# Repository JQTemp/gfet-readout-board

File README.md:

# Nanoamp readout for graphene FET sensors

A low-noise data acquisition board that measures currents of a few nanoamps from a graphene field-effect transistor chip. I led the electronics and took the board through two hardware versions.

| | |
|---|---|
| My role | Electronics lead, covering circuit design, layout, enclosure, bench testing and test software |
| Channels | 6 on V2, 14 on V1 |
| Current range | 5 to 25 nA |
| Resolution | 0.5 nA, measured |
| Inaccuracy | 0.05 to 0.1% in initial bench tests |
| Conversion | MCP3208, 12-bit, SPI, 3.3 V reference |
| Board | Two layers, 79 × 74 mm |
| Tools | KiCad, 3D printing, Python with PyVISA, MATLAB, Keithley source-measure units and multimeter |

## Context

I led the electronics for DeTectUs, a multidisciplinary DTU team taking part in SensUs, an international student competition for sensor prototypes. The team built its sensor around a commercial graphene FET chip from Graphenea with 14 channels. Most of the team worked on functionalising the graphene surface, while I was responsible for the hardware that reads the chip out.

The board holds each channel at a small fixed bias, sweeps the gate voltage and records the channel current, which sits between 5 and 25 nA. The signal is a shift in the gate voltage where the current reaches its minimum, known as the Dirac point.

## Signal chain

Every channel runs through the same chain. A TLC2274 transimpedance amplifier turns the channel current into a voltage, a second TLC2274 stage inverts it into the range of the ADC and an RC low-pass filter at about 10 Hz removes interference and prevents aliasing. A 12-bit MCP3208 ADC converts all six channels and a Raspberry Pi 4 reads it over SPI.

An external 12 V supply keeps mains conversion off the board. An MCP1702 LDO makes 5 V, a MAX1673 charge pump makes −5 V for the op-amps and an LP2950 LDO makes 3.3 V for the ADC and the digital potentiometer. A MAX6250 precision reference and a resistor divider set a fixed 100 mV channel bias. The on-board gate potentiometer was not finished in time, so a bench source-measure unit swept the gate during testing.

## From V1 to V2

V1 was a 154 × 121 mm board with 14 channels, an STM32 Nucleo board for conversion and control and two SPI digital potentiometers for the gate and bias. Measurements on the chips showed that channels 8 to 14 gave unstable readings. V2 reads six channels, adds the inverting stage, moves conversion to a dedicated 12-bit ADC and hands control to a Raspberry Pi 4. The chip socket sits next to the analog front end, the power section runs along the bottom edge and the bottom layer is a ground pour.

## Enclosure

I also designed the enclosure that turns the board into a standalone device. The 3D-printed base, 200 × 154 mm, holds the readout board next to a Raspberry Pi 4, and a tilted housing above them carries the display. The front stays open, so the chip socket can be reached to swap chips.

| Base with the V2 board and a Raspberry Pi 4 | With the display housing in place |
|---|---|
|  |  |

## Testing

Alongside the boards I built an automated bench setup to characterise the graphene FET chips themselves. A Python script controls two Keithley source-measure units over GPIB with PyVISA, one holding the bias across the channel and one sweeping the gate, and logs the drain current at every step. A MATLAB script then finds the Dirac point in each sweep. After the first sweep in each direction the Dirac point repeats at the same gate voltage, within the 12.5 mV step size, and backward sweeps find it about 60 mV higher than forward ones.

Both versions were built and tested on the bench, with a Keithley source-measure unit sweeping the gate and a Keithley multimeter reading the output, scripted in Python with PyVISA. In the first tests the readout stayed within 0.05 to 0.1% across the 5 to 25 nA range and resolved changes of 0.5 nA. The system was finished only a few days before the competition, so these results come from a small number of runs and the board was not used at the event itself.

## Repository contents

- `hardware/v2` KiCad 6 project for V2 (schematic, layout and project file)
- `hardware/v1` KiCad 6 project for V1
- `mechanical` STL files of the latest enclosure parts (base v9, top v8 in two parts)
- `software/bench` Python scripts for the gate sweeps, `testv3.py` for the chips and `testv3pcb.py` for the board
- `software/analysis` MATLAB scripts that find the Dirac point in each sweep
- `data` the gate sweeps shown above as CSV
- `images` renders, diagram, chart and photo used on this page

The board images are rendered directly from the KiCad layouts. The scripts are kept as they were used in the project.

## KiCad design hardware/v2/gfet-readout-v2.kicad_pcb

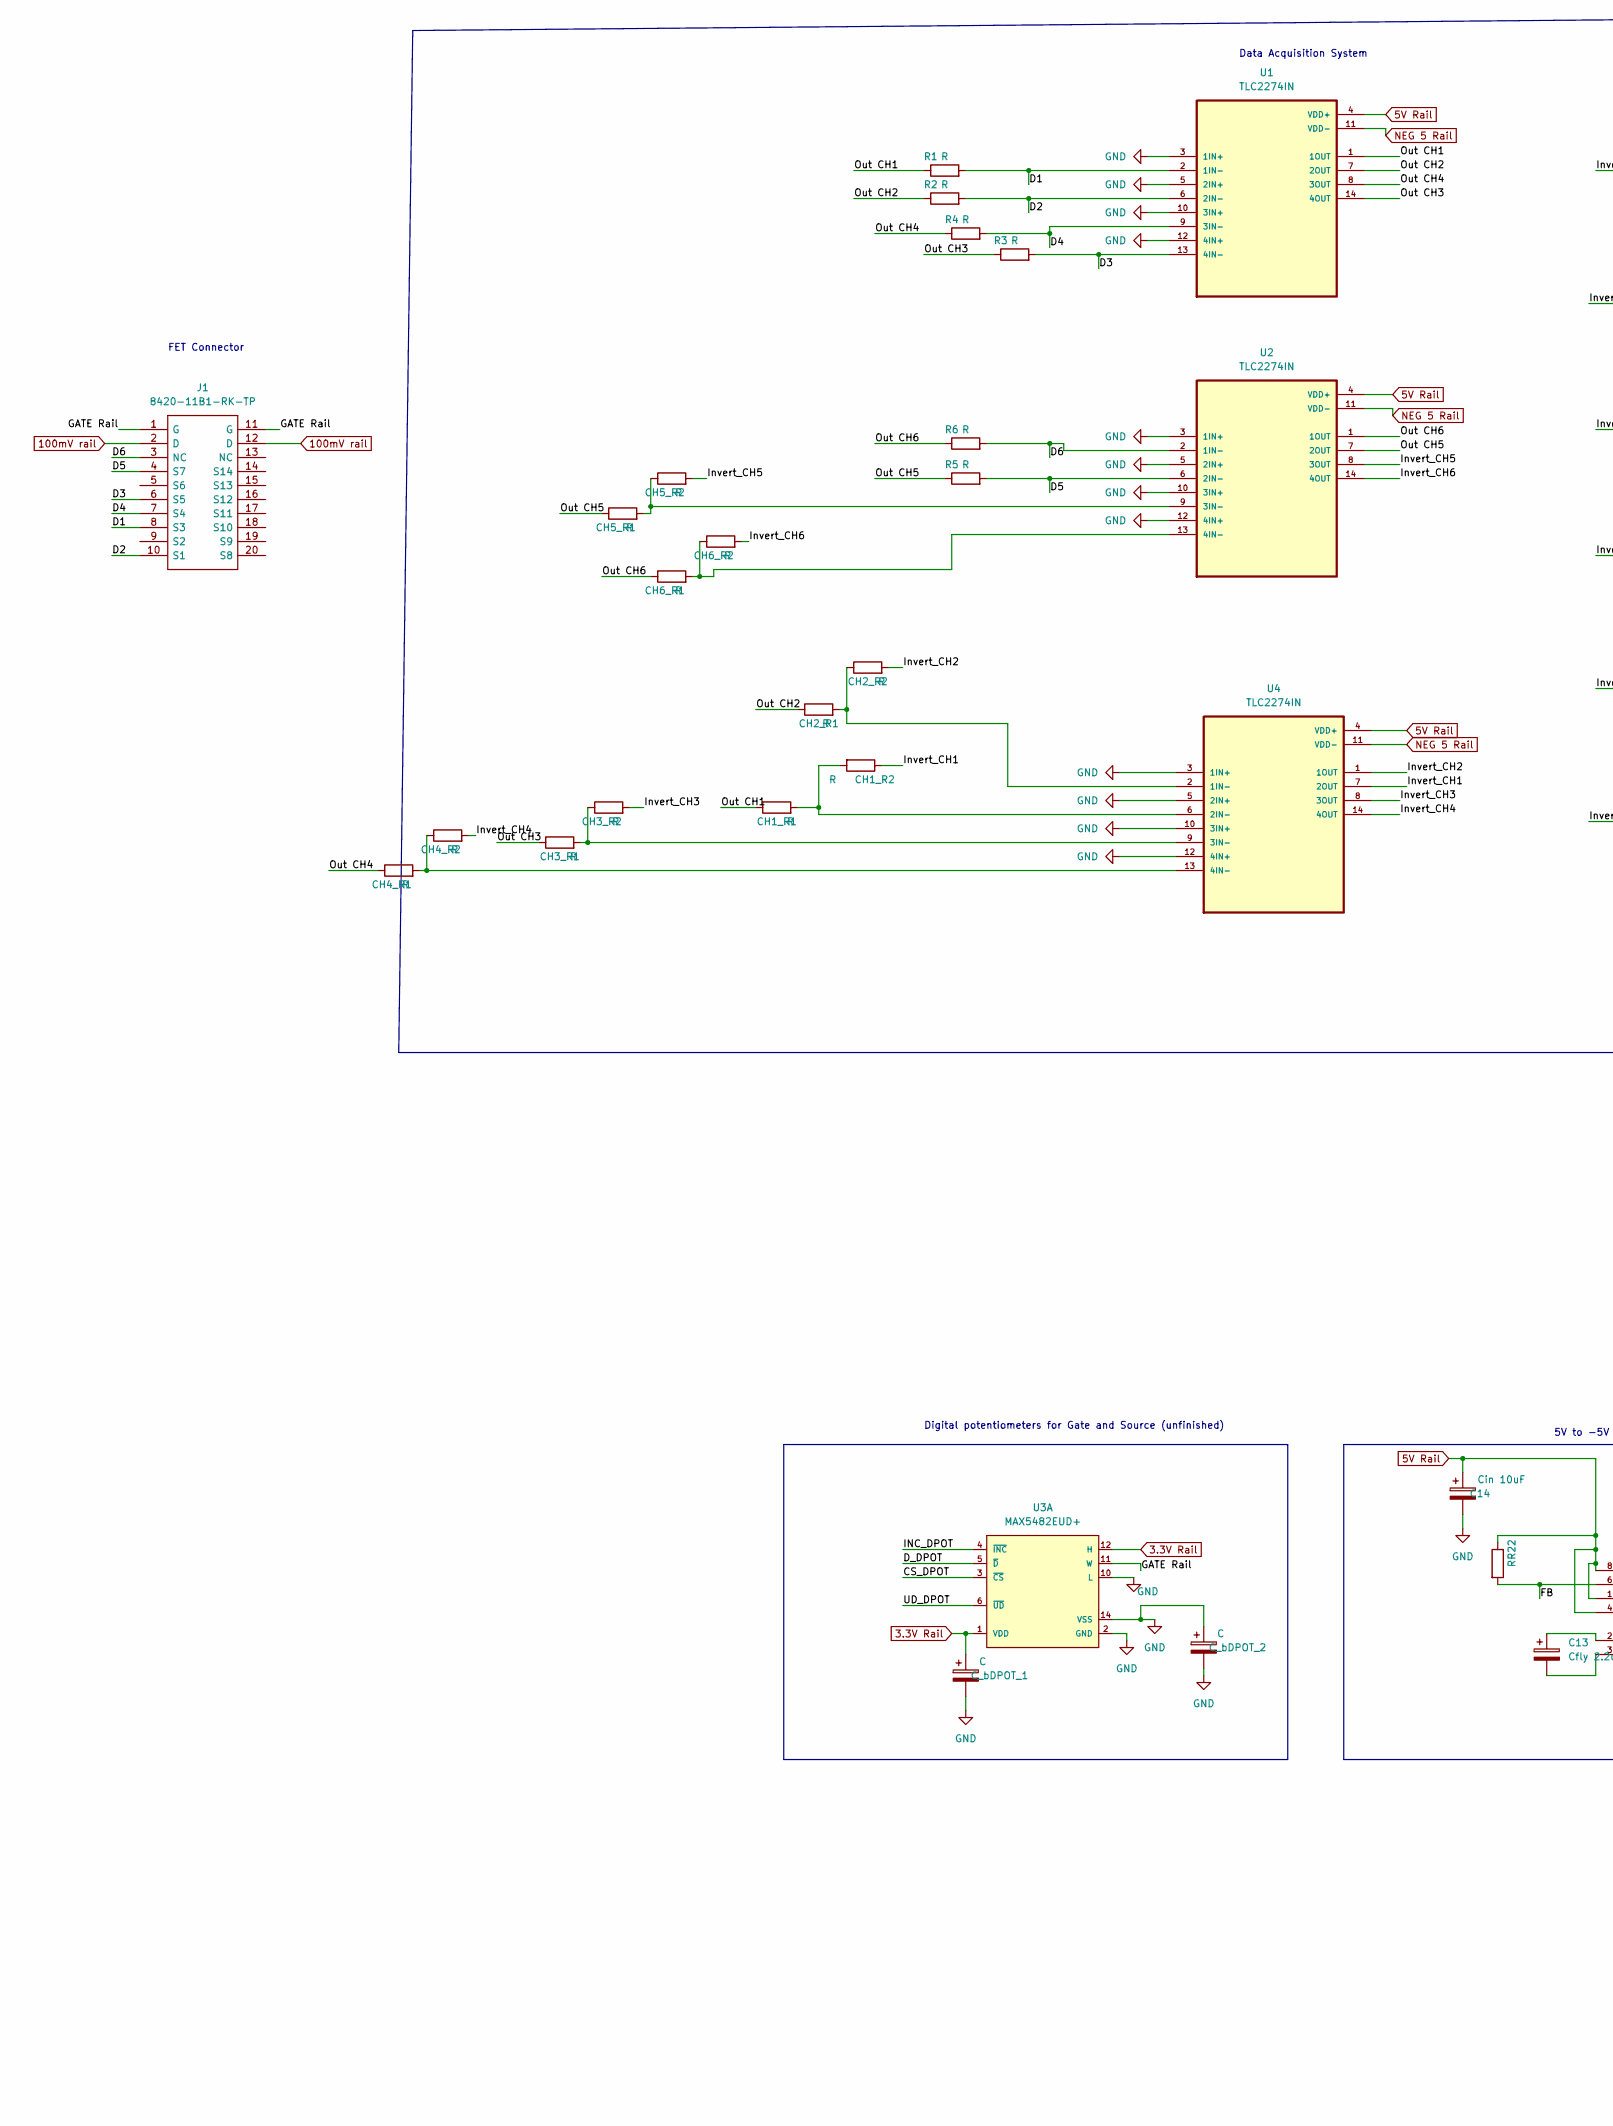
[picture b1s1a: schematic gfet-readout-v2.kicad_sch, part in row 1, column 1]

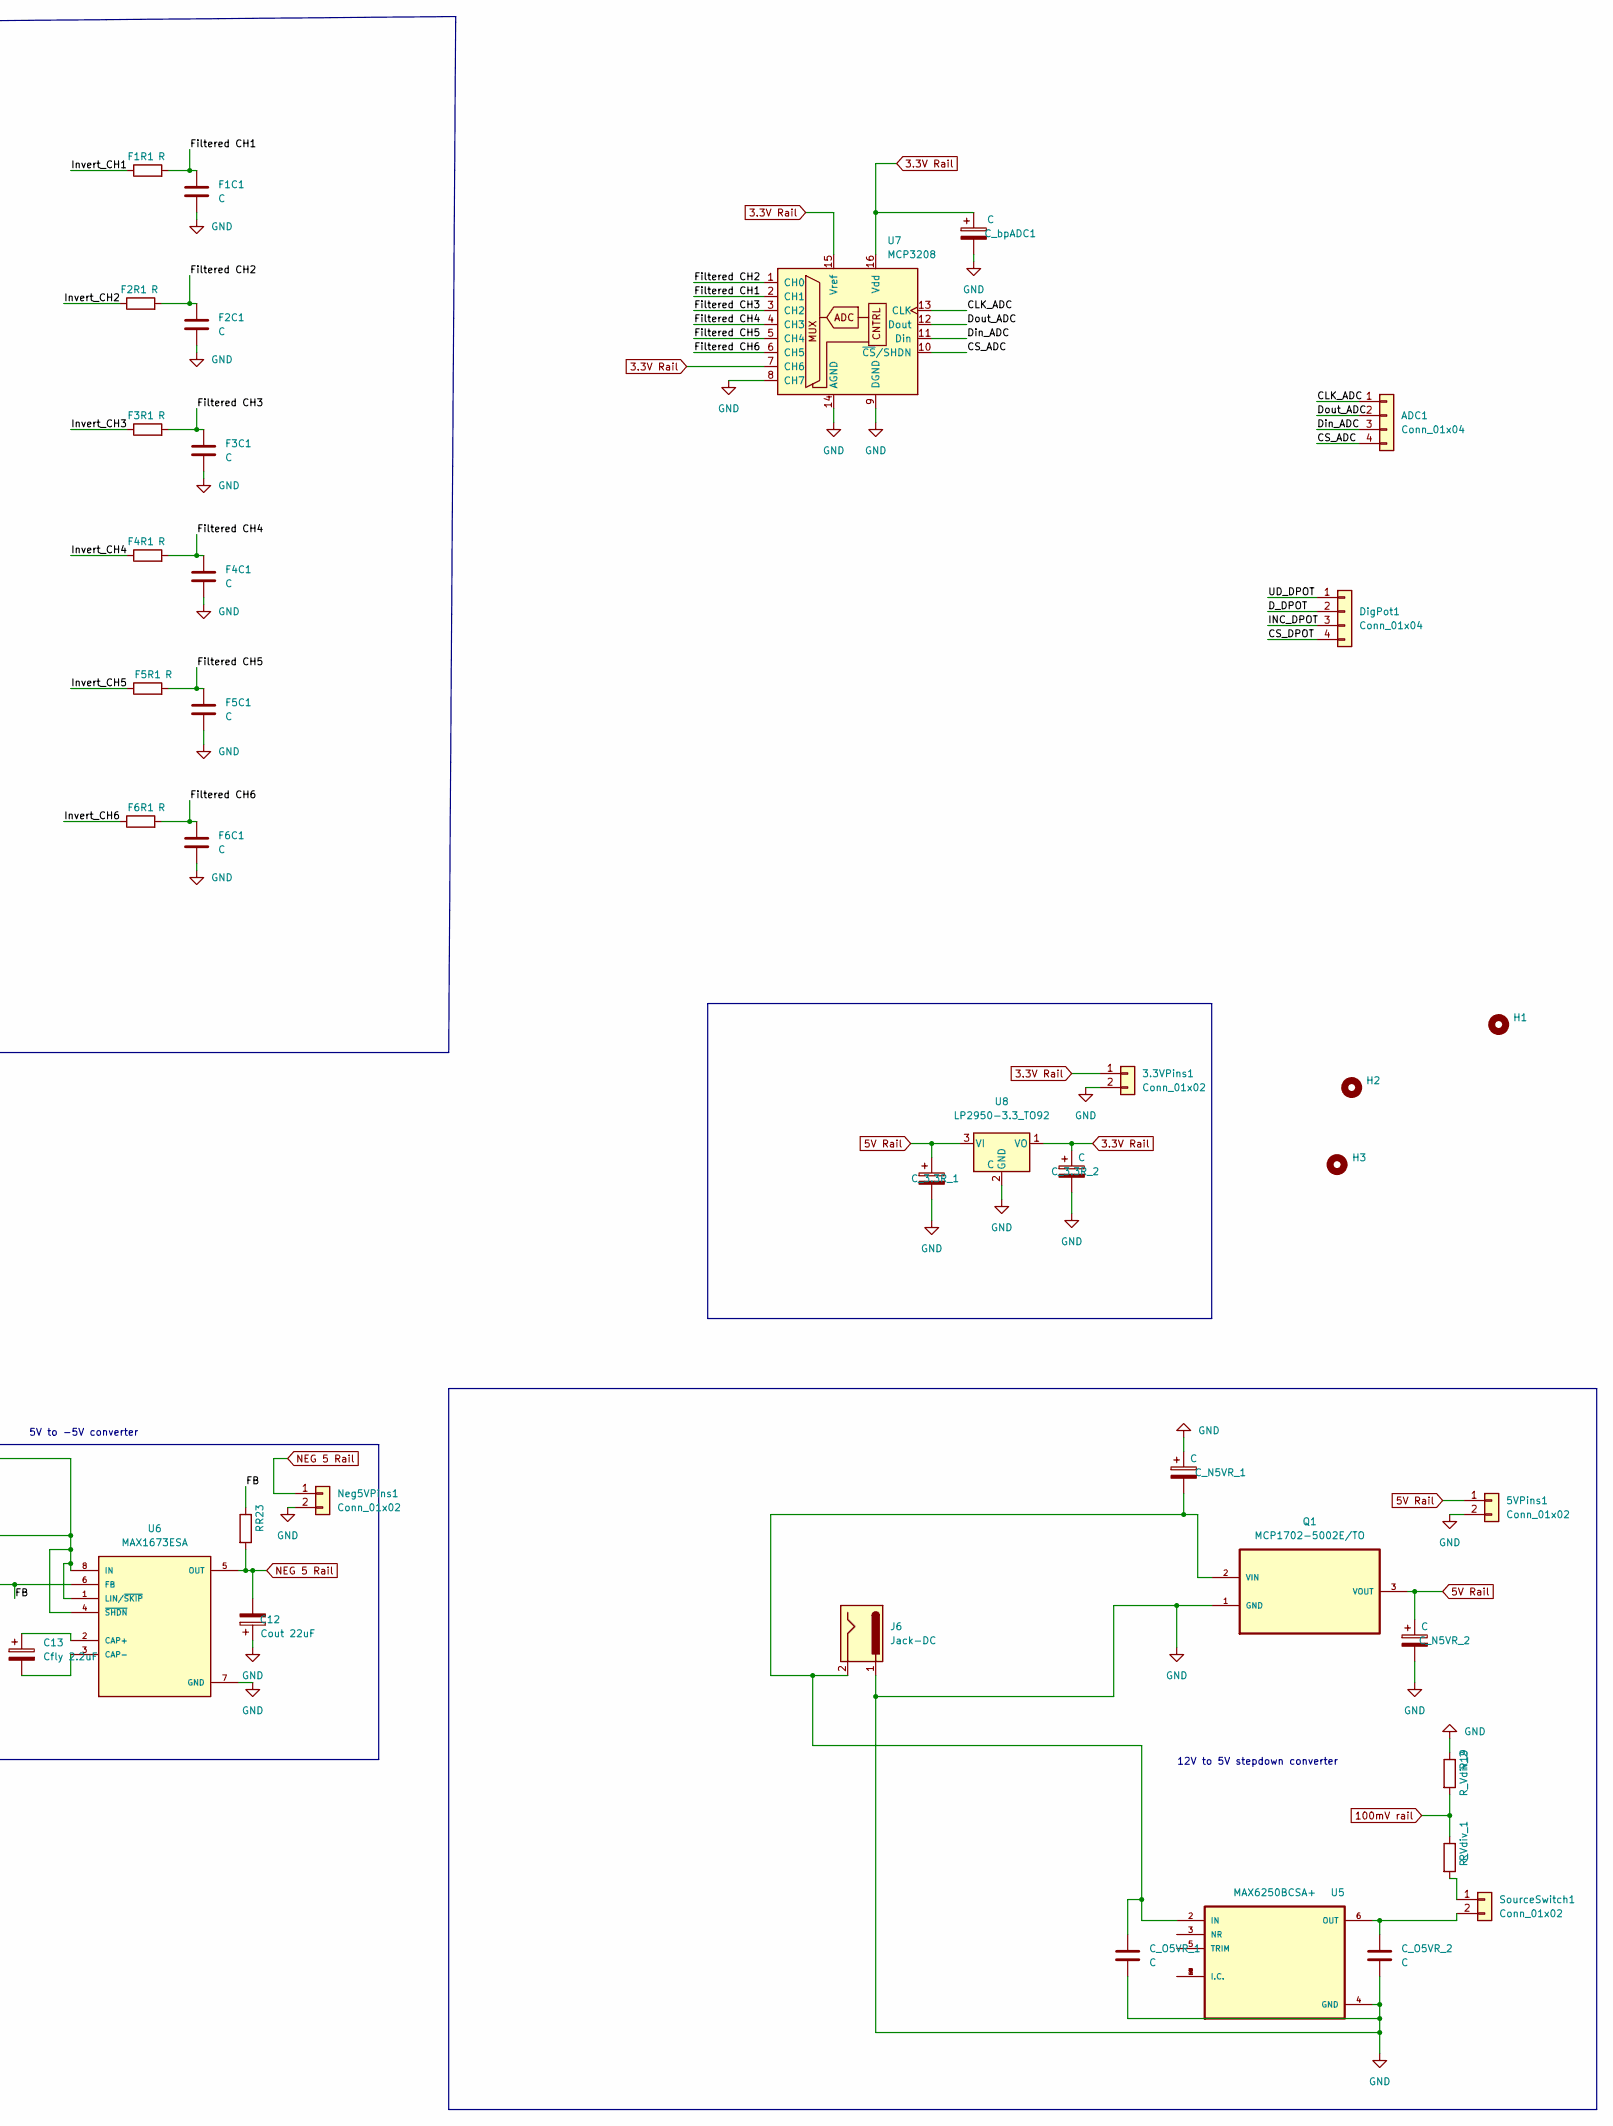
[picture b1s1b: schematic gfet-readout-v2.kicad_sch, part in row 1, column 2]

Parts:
3.3VPins1, 5VPins1: Conn_01x02; PinHeader_1x02_P2.54mm_Vertical
ADC1: Conn_01x04; PinHeader_1x04_P2.54mm_Vertical
C12: Cout 22uF; C_1206_3216Metric_Pad1.33x1.80mm_HandSolder
C13: Cfly 2.2uF; C_0603_1608Metric_Pad1.08x0.95mm_HandSolder
C14: Cin 10uF; C_0805_2012Metric_Pad1.18x1.45mm_HandSolder
CH1_R1, CH1_R2, CH2_R1, CH2_R2, CH3_R1, CH3_R2, CH4_R1, CH4_R2, CH5_R1, CH5_R2, CH6_R1, CH6_R2: R; R_0805_2012Metric_Pad1.20x1.40mm_HandSolder
C_3.3R_1, C_3.3R_2: C; C_0805_2012Metric_Pad1.18x1.45mm_HandSolder
C_N5VR_1, C_N5VR_2: C; C_0805_2012Metric_Pad1.18x1.45mm_HandSolder
C_O5VR_1, C_O5VR_2: C; C_0603_1608Metric_Pad1.08x0.95mm_HandSolder
C_bDPOT_1, C_bDPOT_2: C; C_0805_2012Metric_Pad1.18x1.45mm_HandSolder
C_bpADC1: C; C_0805_2012Metric_Pad1.18x1.45mm_HandSolder
DigPot1: Conn_01x04; PinHeader_1x04_P2.54mm_Vertical
F1C1, F2C1, F3C1, F4C1, F5C1, F6C1: C; C_0805_2012Metric_Pad1.18x1.45mm_HandSolder
F1R1, F2R1, F3R1, F4R1, F5R1, F6R1: R; R_0805_2012Metric_Pad1.20x1.40mm_HandSolder
H1, H2, H3: MountingHole_2.2mm_M2
J1: 8420-11B1-RK-TP; 842011B1RKTP; Mouser Part Number 517-8420-11B1-RK-TP
J6: Jack-DC; BarrelJack_GCT_DCJ200-10-A_Horizontal
Neg5VPins1: Conn_01x02; PinHeader_1x02_P2.54mm_Vertical
Q1: MCP1702-5002E/TO; TO127P254X533-3; MPN MCP1702-5002E/TO
R1, R2, R3, R4, R5, R6, R22, R23: R; R_0805_2012Metric_Pad1.20x1.40mm_HandSolder
R19: R_Vdiv_2; R_0805_2012Metric_Pad1.20x1.40mm_HandSolder
R_Vdiv_1: R; R_0805_2012Metric_Pad1.20x1.40mm_HandSolder
SourceSwitch1: Conn_01x02; PinHeader_1x02_P2.54mm_Vertical
U1, U2, U4: TLC2274IN; DIP794W45P254L1969H508Q14
U3: MAX5482EUD+; Maxim-MAX5481EUD+-Level_B
U5: MAX6250BCSA+; SOIC127P600X175-8N
U6: MAX1673ESA; SOIC127P600X175-8N; PARTREV 0
U7: MCP3208; DIP-16_W7.62mm
U8: LP2950-3.3_TO92; TO-92_Inline

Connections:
3.3V Rail: 3.3VPins1.1, C_3.3R_2.1, C_bDPOT_1.1, C_bpADC1.1, U3.1 (VDD), U3.12 (H), U7.7 (CH6), U7.15 (Vref), U7.16 (Vdd), U8.1 (VO)
5V Rail: 5VPins1.1, C14.1, C_3.3R_1.1, C_N5VR_2.1, Q1.3 (VOUT), R22.1, U1.4 (VDD+), U2.4 (VDD+), U4.4 (VDD+), U6.1 (LIN/~SKIP), U6.4 (~SHDN), U6.8 (IN), U8.3 (VI)
100mV rail: J1.2 (D), J1.12 (D), R19.2, R_Vdiv_1.1
/CLK_ADC: ADC1.1, U7.13 (CLK)
/CS_ADC: ADC1.4, U7.10 (~CS/SHDN)
/CS_DPOT: DigPot1.4, U3.3 (~CS)
/D1: J1.8 (S3), R1.2, U1.2 (1IN-)
/D2: J1.10 (S1), R2.2, U1.6 (2IN-)
/D3: J1.6 (S5), R3.2, U1.13 (4IN-)
/D4: J1.7 (S4), R4.2, U1.9 (3IN-)
/D5: J1.4 (S7), R5.2, U2.6 (2IN-)
/D6: J1.3 (NC), R6.2, U2.2 (1IN-)
/D_DPOT: DigPot1.2, U3.5 (~D)
/Din_ADC: ADC1.3, U7.11 (Din)
/Dout_ADC: ADC1.2, U7.12 (Dout)
/FB: R22.2, R23.1, U6.6 (FB)
/Filtered CH1: F1C1.1, F1R1.2, U7.2 (CH1)
/Filtered CH2: F2C1.1, F2R1.2, U7.1 (CH0)
/Filtered CH3: F3C1.1, F3R1.2, U7.3 (CH2)
/Filtered CH4: F4C1.1, F4R1.2, U7.4 (CH3)
/Filtered CH5: F5C1.1, F5R1.2, U7.5 (CH4)
/Filtered CH6: F6C1.1, F6R1.2, U7.6 (CH5)
/GATE Rail: J1.1 (G), J1.11 (G), U3.11 (W)
/INC_DPOT: DigPot1.3, U3.4 (~INC)
/Invert_CH1: CH1_R2.1, F1R1.1, U4.7 (2OUT)
/Invert_CH2: CH2_R2.2, F2R1.1, U4.1 (1OUT)
/Invert_CH3: CH3_R2.2, F3R1.1, U4.8 (3OUT)
/Invert_CH4: CH4_R2.2, F4R1.1, U4.14 (4OUT)
/Invert_CH5: CH5_R2.2, F5R1.1, U2.8 (3OUT)
/Invert_CH6: CH6_R2.2, F6R1.1, U2.14 (4OUT)
/Out CH1: CH1_R1.1, R1.1, U1.1 (1OUT)
/Out CH2: CH2_R1.1, R2.1, U1.7 (2OUT)
/Out CH3: CH3_R1.1, R3.1, U1.14 (4OUT)
/Out CH4: CH4_R1.1, R4.1, U1.8 (3OUT)
/Out CH5: CH5_R1.1, R5.1, U2.7 (2OUT)
/Out CH6: CH6_R1.1, R6.1, U2.1 (1OUT)
/UD_DPOT: DigPot1.1, U3.6 (~UD)
GND: 3.3VPins1.2, 5VPins1.2, C12.1, C14.2, C_3.3R_1.2, C_3.3R_2.2, C_N5VR_1.1, C_N5VR_2.2, C_O5VR_1.2, C_O5VR_2.2, C_bDPOT_1.2, C_bDPOT_2.1, C_bDPOT_2.2, C_bpADC1.2, F1C1.2, F2C1.2, F3C1.2, F4C1.2, F5C1.2, F6C1.2, J6.1, Neg5VPins1.2, Q1.1 (GND), R19.1, U1.3 (1IN+), U1.5 (2IN+), U1.10 (3IN+), U1.12 (4IN+), U2.3 (1IN+), U2.5 (2IN+), U2.10 (3IN+), U2.12 (4IN+), U3.2 (GND), U3.10 (L), U3.14 (VSS), U4.3 (1IN+), U4.5 (2IN+), U4.10 (3IN+), U4.12 (4IN+), U5.4 (GND), U6.7 (GND), U7.8 (CH7), U7.9 (DGND), U7.14 (AGND), U8.2 (GND)
NEG 5 Rail: C12.2, Neg5VPins1.1, R23.2, U1.11 (VDD-), U2.11 (VDD-), U4.11 (VDD-), U6.5 (OUT)
unnamed: C13.1, U6.2 (CAP+)
unnamed: C13.2, U6.3 (CAP-)
unnamed: CH1_R1.2, CH1_R2.2, U4.6 (2IN-)
unnamed: CH3_R1.2, CH3_R2.1, U4.9 (3IN-)
unnamed: CH4_R1.2, CH4_R2.1, U4.13 (4IN-)
unnamed: CH5_R1.2, CH5_R2.1, U2.9 (3IN-)
unnamed: CH6_R1.2, CH6_R2.1, U2.13 (4IN-)
unnamed: C_N5VR_1.2, C_O5VR_1.1, J6.2, Q1.2 (VIN), U5.2 (IN)
unnamed 47: R_Vdiv_1.2, SourceSwitch1.1; also elsewhere on the board
unnamed: CH2_R1.2, CH2_R2.1, U4.2 (1IN-)
unnamed: U5.1 (I.C.), U5.7 (I.C.), U5.8 (I.C.)
unnamed 50: C_O5VR_2.1, SourceSwitch1.2, U5.6 (OUT); also elsewhere on the board

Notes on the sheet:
Digital potentiometers for Gate and Source (unfinished)
FET Connector
5V to -5V converter
12V to 5V stepdown converter
Data Acquisition System

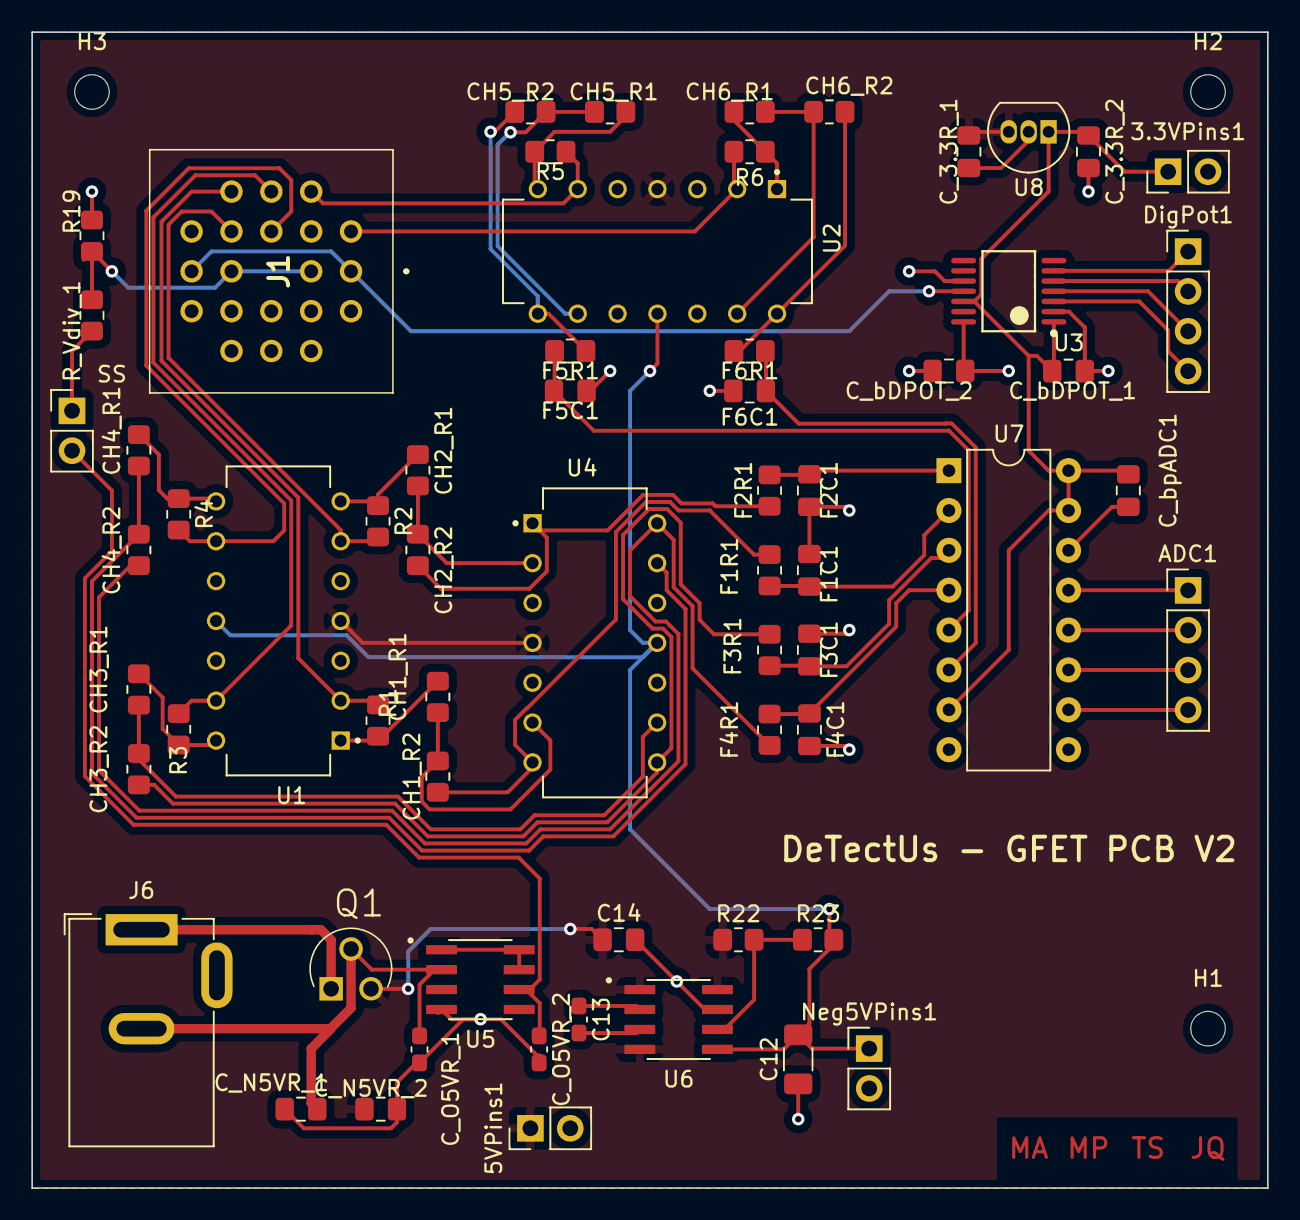
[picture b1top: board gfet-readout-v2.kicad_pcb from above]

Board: 2 copper layers, 78.7 x 73.7 mm, 66 parts (0 on the bottom side), 51 nets.

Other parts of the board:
SS: Conn_01x02; PinHeader_1x02_P2.54mm_Vertical

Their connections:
unnamed 47: SS.1; also elsewhere on the board
unnamed 50: SS.2; also elsewhere on the board

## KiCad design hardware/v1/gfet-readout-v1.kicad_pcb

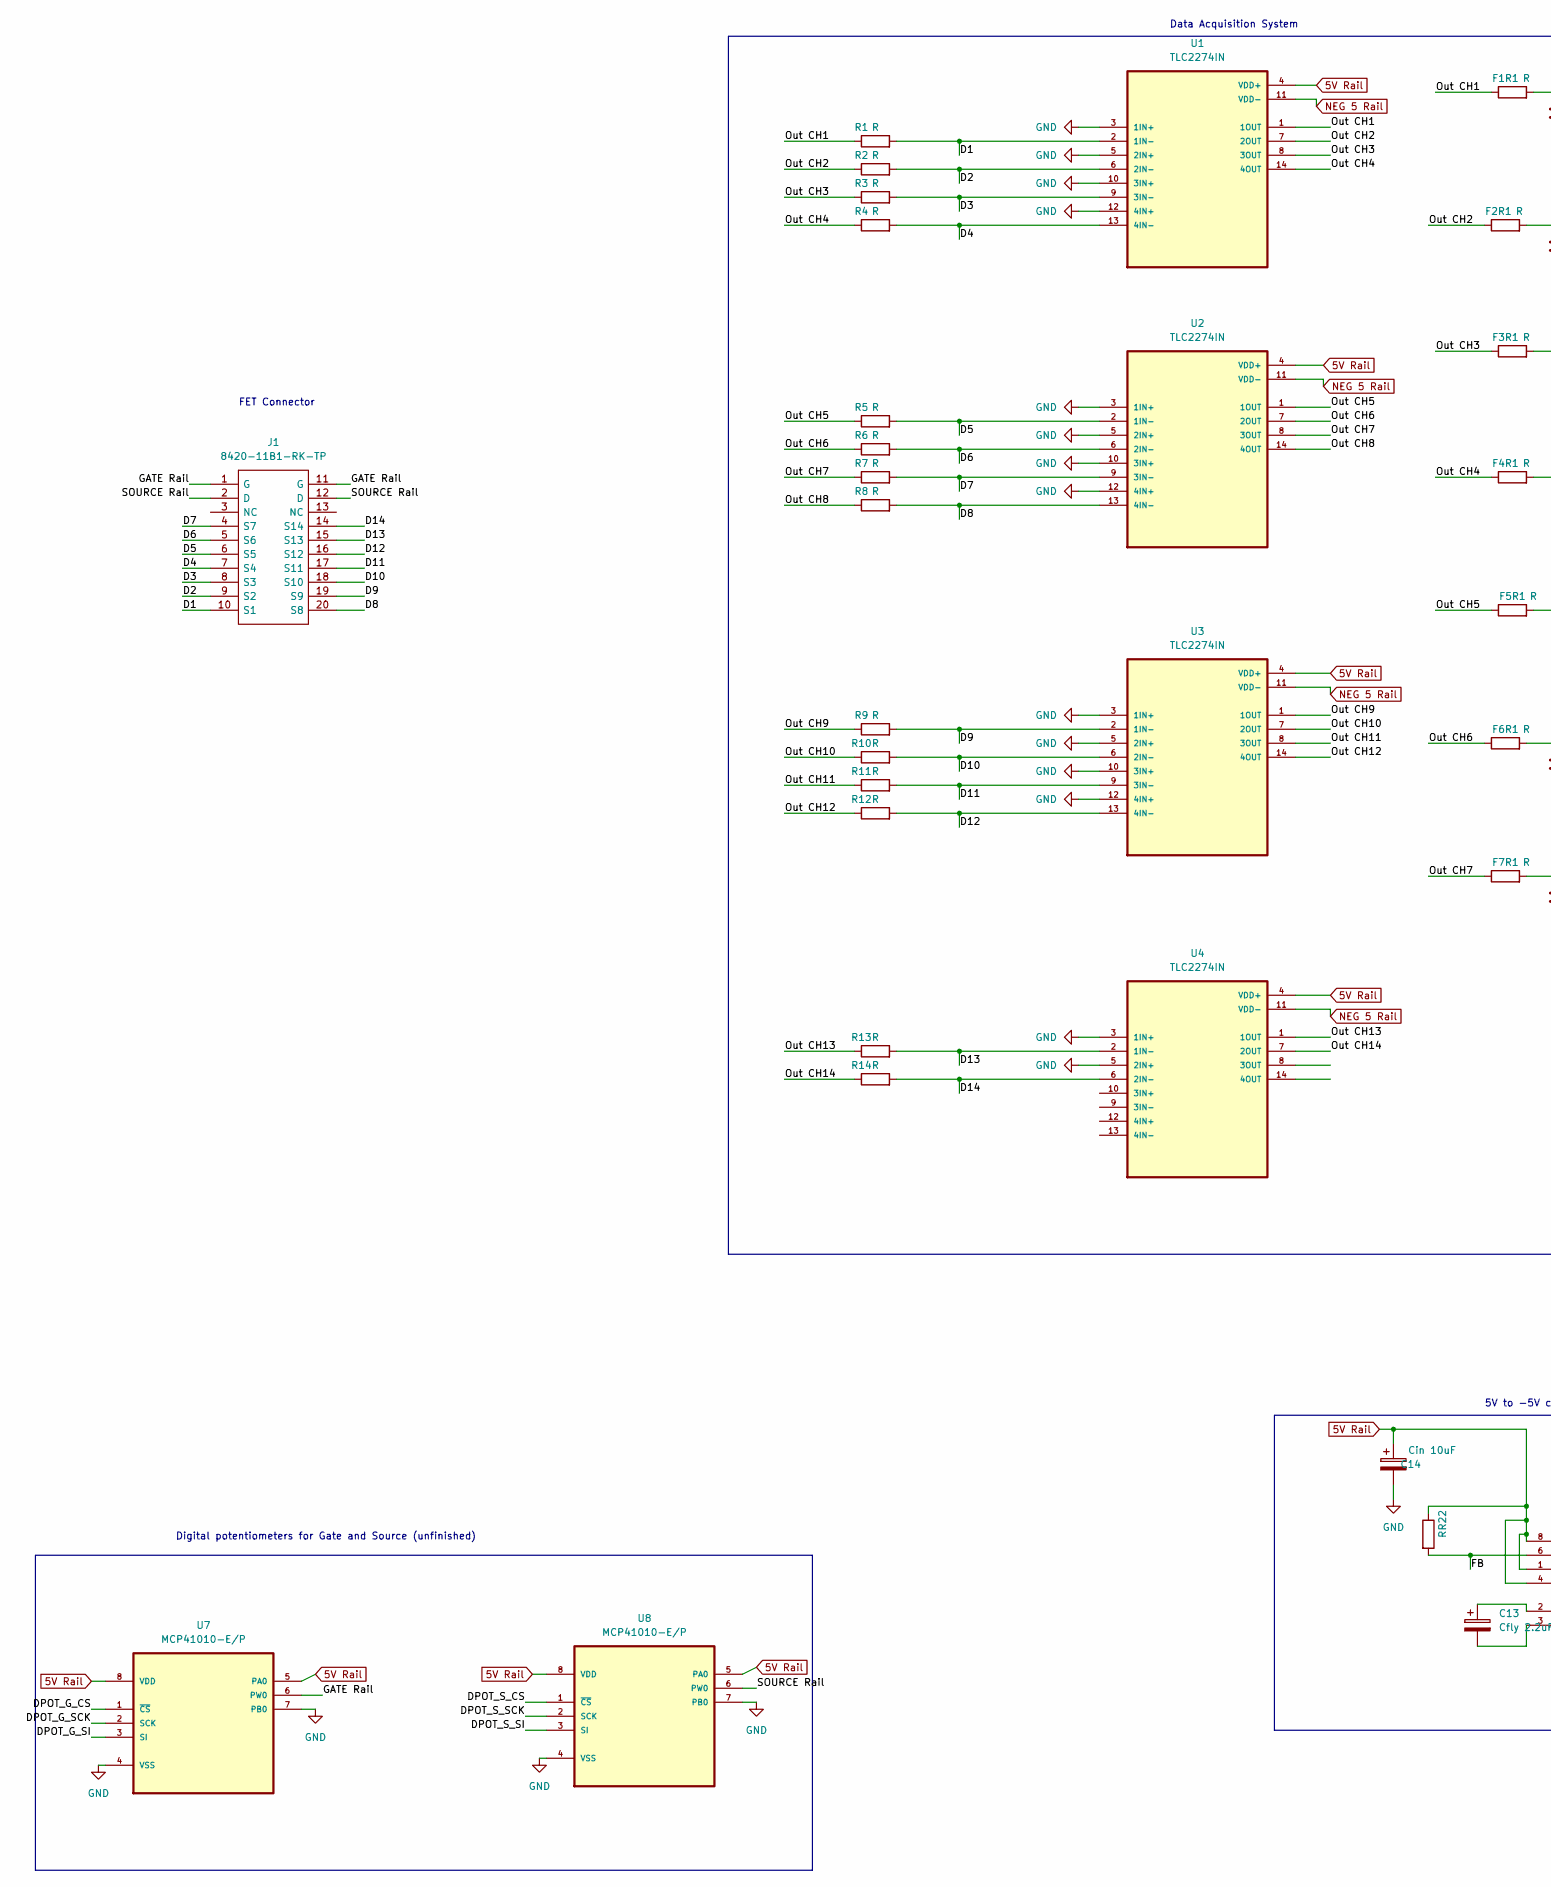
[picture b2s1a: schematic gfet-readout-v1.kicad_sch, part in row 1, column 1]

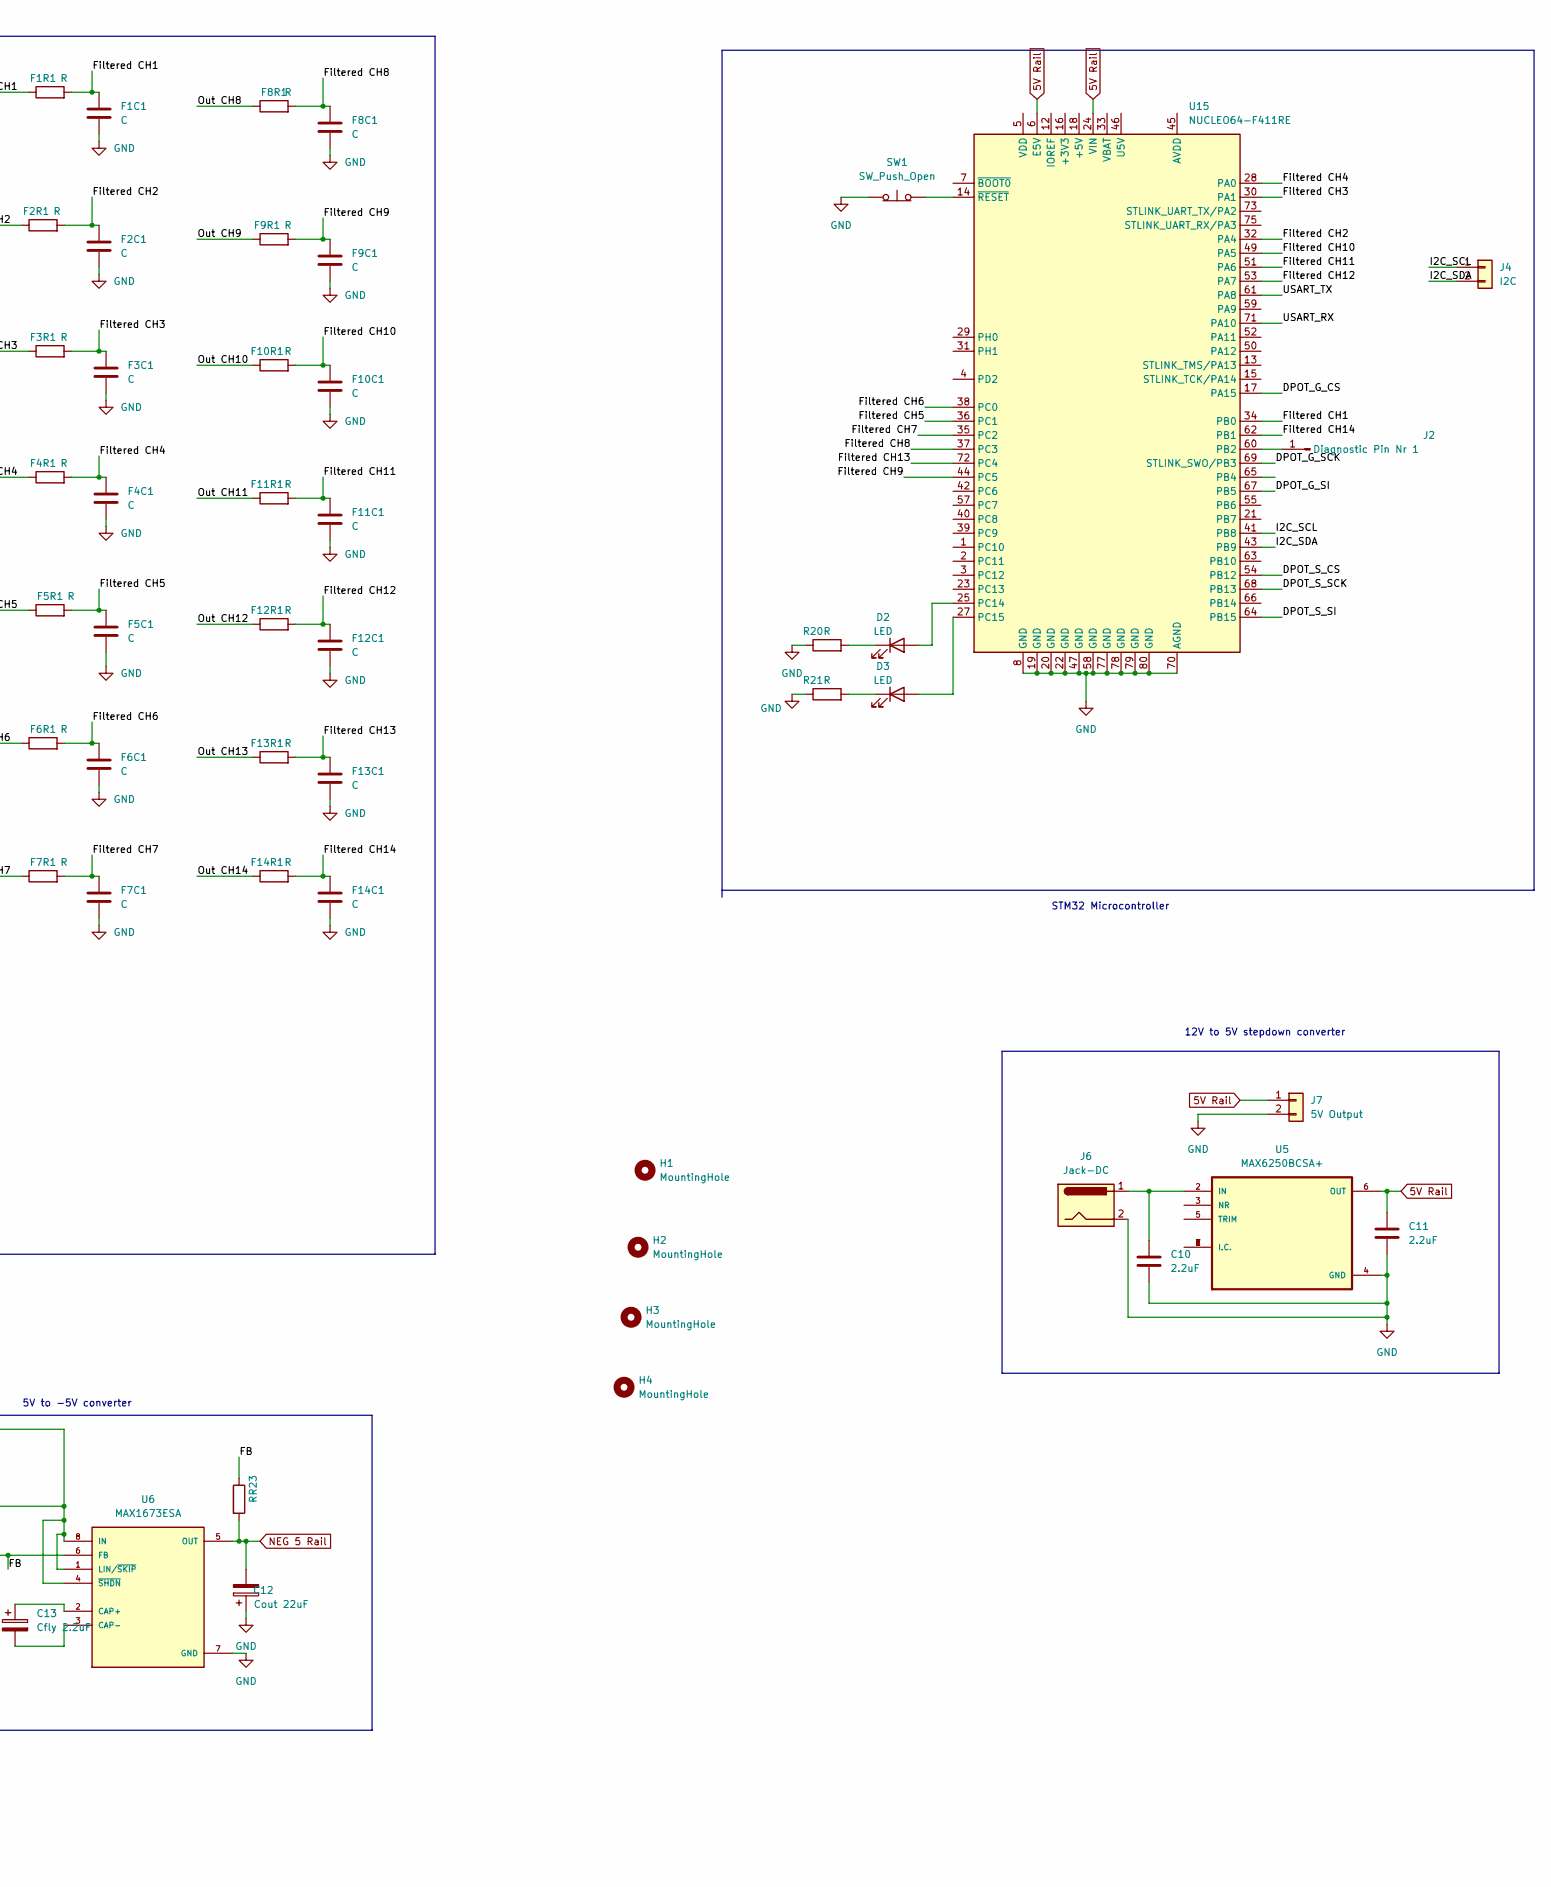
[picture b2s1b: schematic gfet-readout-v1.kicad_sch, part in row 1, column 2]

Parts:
C10, C11: 2.2uF; C_0603_1608Metric_Pad1.08x0.95mm_HandSolder
C12: Cout 22uF; C_1206_3216Metric_Pad1.33x1.80mm_HandSolder
C13: Cfly 2.2uF; C_0603_1608Metric_Pad1.08x0.95mm_HandSolder
C14: Cin 10uF; C_0805_2012Metric_Pad1.18x1.45mm_HandSolder
D2, D3: LED; LED_D5.0mm
F1C1, F2C1, F3C1, F4C1, F5C1, F6C1, F7C1, F8C1, F9C1, F10C1, F11C1, F12C1, F13C1, F14C1: C; C_0805_2012Metric_Pad1.18x1.45mm_HandSolder
F1R1, F2R1, F3R1, F4R1, F5R1, F6R1, F7R1, F8R1, F9R1, F10R1, F11R1, F12R1, F13R1, F14R1: R; R_0805_2012Metric_Pad1.20x1.40mm_HandSolder
H1, H2, H3, H4: MountingHole; MountingHole_4.3mm_M4
J1: 8420-11B1-RK-TP; 842011B1RKTP; Mouser Part Number 517-8420-11B1-RK-TP
J2: Diagnostic Pin Nr 1; Pin_D0.9mm_L10.0mm_W2.4mm_FlatFork
J4: I2C; PinHeader_1x02_P2.54mm_Vertical
J6: Jack-DC; BarrelJack_GCT_DCJ200-10-A_Horizontal
J7: 5V Output; PinHeader_1x02_P2.54mm_Vertical
R1, R2, R3, R4, R5, R6, R7, R8, R9, R10, R11, R12, R13, R14, R20, R21, R22, R23: R; R_0805_2012Metric_Pad1.20x1.40mm_HandSolder
SW1: SW_Push_Open; SW_PUSH_6mm
U1, U2, U3, U4: TLC2274IN; DIP794W45P254L1969H508Q14
U5: MAX6250BCSA+; SOIC127P600X175-8N
U6: MAX1673ESA; SOIC127P600X175-8N; PARTREV 0
U7, U8: MCP41010-E/P; DIP254P762X432-8; MPN MCP41010-E/P
U15: NUCLEO64-F411RE; ST_Morpho_Connector_144_STLink

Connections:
5V Rail: C11.1, C14.1, J7.1, R22.1, U1.4 (VDD+), U2.4 (VDD+), U3.4 (VDD+), U4.4 (VDD+), U5.6 (OUT), U6.1 (LIN/~SKIP), U6.4 (~SHDN), U6.8 (IN), U7.5 (PA0), U7.8 (VDD), U8.5 (PA0), U8.8 (VDD), U15.6 (E5V), U15.24 (VIN)
/D1: J1.10 (S1), R1.2, U1.2 (1IN-)
/D2: J1.9 (S2), R2.2, U1.6 (2IN-)
/D3: J1.8 (S3), R3.2, U1.9 (3IN-)
/D4: J1.7 (S4), R4.2, U1.13 (4IN-)
/D5: J1.6 (S5), R5.2, U2.2 (1IN-)
/D6: J1.5 (S6), R6.2, U2.6 (2IN-)
/D7: J1.4 (S7), R7.2, U2.9 (3IN-)
/D8: J1.20 (S8), R8.2, U2.13 (4IN-)
/D9: J1.19 (S9), R9.2, U3.2 (1IN-)
/D10: J1.18 (S10), R10.2, U3.6 (2IN-)
/D11: J1.17 (S11), R11.2, U3.9 (3IN-)
/D12: J1.16 (S12), R12.2, U3.13 (4IN-)
/D13: J1.15 (S13), R13.2, U4.2 (1IN-)
/D14: J1.14 (S14), R14.2, U4.6 (2IN-)
/DPOT_G_CS: U7.1 (~CS), U15.17 (PA15)
/DPOT_G_SCK: U7.2 (SCK), U15.69 (STLINK_SWO/PB3)
/DPOT_G_SI: U7.3 (SI), U15.67 (PB5)
/DPOT_S_CS: U8.1 (~CS), U15.54 (PB12)
/DPOT_S_SCK: U8.2 (SCK), U15.68 (PB13)
/DPOT_S_SI: U8.3 (SI), U15.64 (PB15)
/FB: R22.2, R23.1, U6.6 (FB)
/Filtered CH1: F1C1.1, F1R1.2, U15.34 (PB0)
/Filtered CH2: F2C1.1, F2R1.2, U15.32 (PA4)
/Filtered CH3: F3C1.1, F3R1.2, U15.30 (PA1)
/Filtered CH4: F4C1.1, F4R1.2, U15.28 (PA0)
/Filtered CH5: F5C1.1, F5R1.2, U15.36 (PC1)
/Filtered CH6: F6C1.1, F6R1.2, U15.38 (PC0)
/Filtered CH7: F7C1.1, F7R1.2, U15.35 (PC2)
/Filtered CH8: F8C1.1, F8R1.2, U15.37 (PC3)
/Filtered CH9: F9C1.1, F9R1.2, U15.44 (PC5)
/Filtered CH10: F10C1.1, F10R1.2, U15.49 (PA5)
/Filtered CH11: F11C1.1, F11R1.2, U15.51 (PA6)
/Filtered CH12: F12C1.1, F12R1.2, U15.53 (PA7)
/Filtered CH13: F13C1.1, F13R1.2, U15.72 (PC4)
/Filtered CH14: F14C1.1, F14R1.2, U15.62 (PB1)
/GATE Rail: J1.1 (G), J1.11 (G), U7.6 (PW0)
/I2C_SCL: J4.1, U15.41 (PB8)
/I2C_SDA: J4.2, U15.43 (PB9)
/Out CH1: F1R1.1, R1.1, U1.1 (1OUT)
/Out CH2: F2R1.1, R2.1, U1.7 (2OUT)
/Out CH3: F3R1.1, R3.1, U1.8 (3OUT)
/Out CH4: F4R1.1, R4.1, U1.14 (4OUT)
/Out CH5: F5R1.1, R5.1, U2.1 (1OUT)
/Out CH6: F6R1.1, R6.1, U2.7 (2OUT)
/Out CH7: F7R1.1, R7.1, U2.8 (3OUT)
/Out CH8: F8R1.1, R8.1, U2.14 (4OUT)
/Out CH9: F9R1.1, R9.1, U3.1 (1OUT)
/Out CH10: F10R1.1, R10.1, U3.7 (2OUT)
/Out CH11: F11R1.1, R11.1, U3.8 (3OUT)
/Out CH12: F12R1.1, R12.1, U3.14 (4OUT)
/Out CH13: F13R1.1, R13.1, U4.1 (1OUT)
/Out CH14: F14R1.1, R14.1, U4.7 (2OUT)
/SOURCE Rail: J1.2 (D), J1.12 (D), U8.6 (PW0)
/USART_RX: U15.71 (PA10)
/USART_TX: U15.61 (PA8)
GND: C10.2, C11.2, C12.1, C14.2, F1C1.2, F2C1.2, F3C1.2, F4C1.2, F5C1.2, F6C1.2, F7C1.2, F8C1.2, F9C1.2, F10C1.2, F11C1.2, F12C1.2, F13C1.2, F14C1.2, J6.2, J7.2, R20.1, R21.1, SW1.1 (A), U1.3 (1IN+), U1.5 (2IN+), U1.10 (3IN+), U1.12 (4IN+), U2.3 (1IN+), U2.5 (2IN+), U2.10 (3IN+), U2.12 (4IN+), U3.3 (1IN+), U3.5 (2IN+), U3.10 (3IN+), U3.12 (4IN+), U4.3 (1IN+), U4.5 (2IN+), U5.4 (GND), U6.7 (GND), U7.4 (VSS), U7.7 (PB0), U8.4 (VSS), U8.7 (PB0), U15.8 (GND), U15.19 (GND), U15.20 (GND), U15.22 (GND), U15.47 (GND), U15.58 (GND), U15.70 (AGND), U15.77 (GND), U15.78 (GND), U15.79 (GND), U15.80 (GND)
NEG 5 Rail: C12.2, R23.2, U1.11 (VDD-), U2.11 (VDD-), U3.11 (VDD-), U4.11 (VDD-), U6.5 (OUT)
unnamed: C10.1, J6.1, U5.2 (IN)
unnamed: C13.1, U6.2 (CAP+)
unnamed: C13.2, U6.3 (CAP-)
unnamed: D2.1 (K), R20.2
unnamed: D2.2 (A), U15.25 (PC14)
unnamed: D3.1 (K), R21.2
unnamed: D3.2 (A), U15.27 (PC15)
unnamed: J2.1, U15.60 (PB2)
unnamed: SW1.2 (B), U15.14 (~RESET)
unnamed: U5.1 (I.C.), U5.7 (I.C.), U5.8 (I.C.)

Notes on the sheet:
STM32 Microcontroller
Digital potentiometers for Gate and Source (unfinished)
FET Connector
5V to -5V converter
12V to 5V stepdown converter
Data Acquisition System
